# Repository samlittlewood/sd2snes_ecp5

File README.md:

Lattice ECP5 Transplant for SD2SNES
===================================

Based on https://github.com/mrehkopf/sd2snes

* Main changes are FPGA, RAM and power. The SNES interface and MCU are broadly the same as SD2SNES
* Prototype is populated with ECP5U-45F for easy development - 12F or 25F parts are available for same footprint. 
* MSU-1 DAC mods from https://github.com/DevLaTron/sd2snes
* USB-C (2.0) connector

Schematic: https://github.com/samlittlewood/sd2snes_ecp5/raw/main/RevB/sd2snes_ecp5.pdf

WARNING: This is still a prototype - it has managed to run games, but more than likely has some 'hilarious in hindsight' mistakes that have yet to be found.

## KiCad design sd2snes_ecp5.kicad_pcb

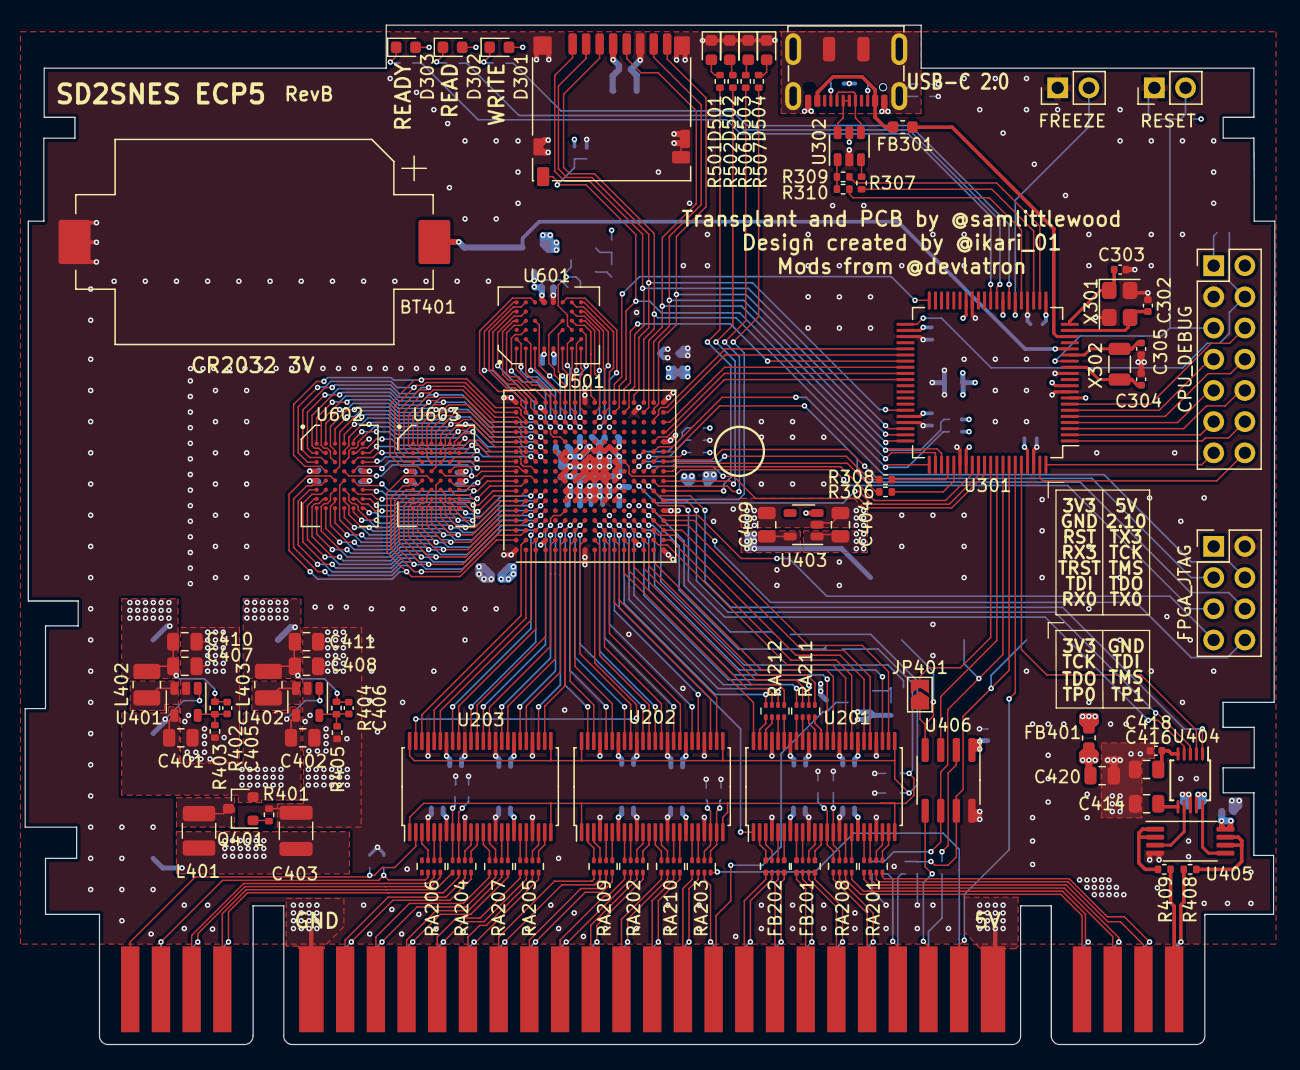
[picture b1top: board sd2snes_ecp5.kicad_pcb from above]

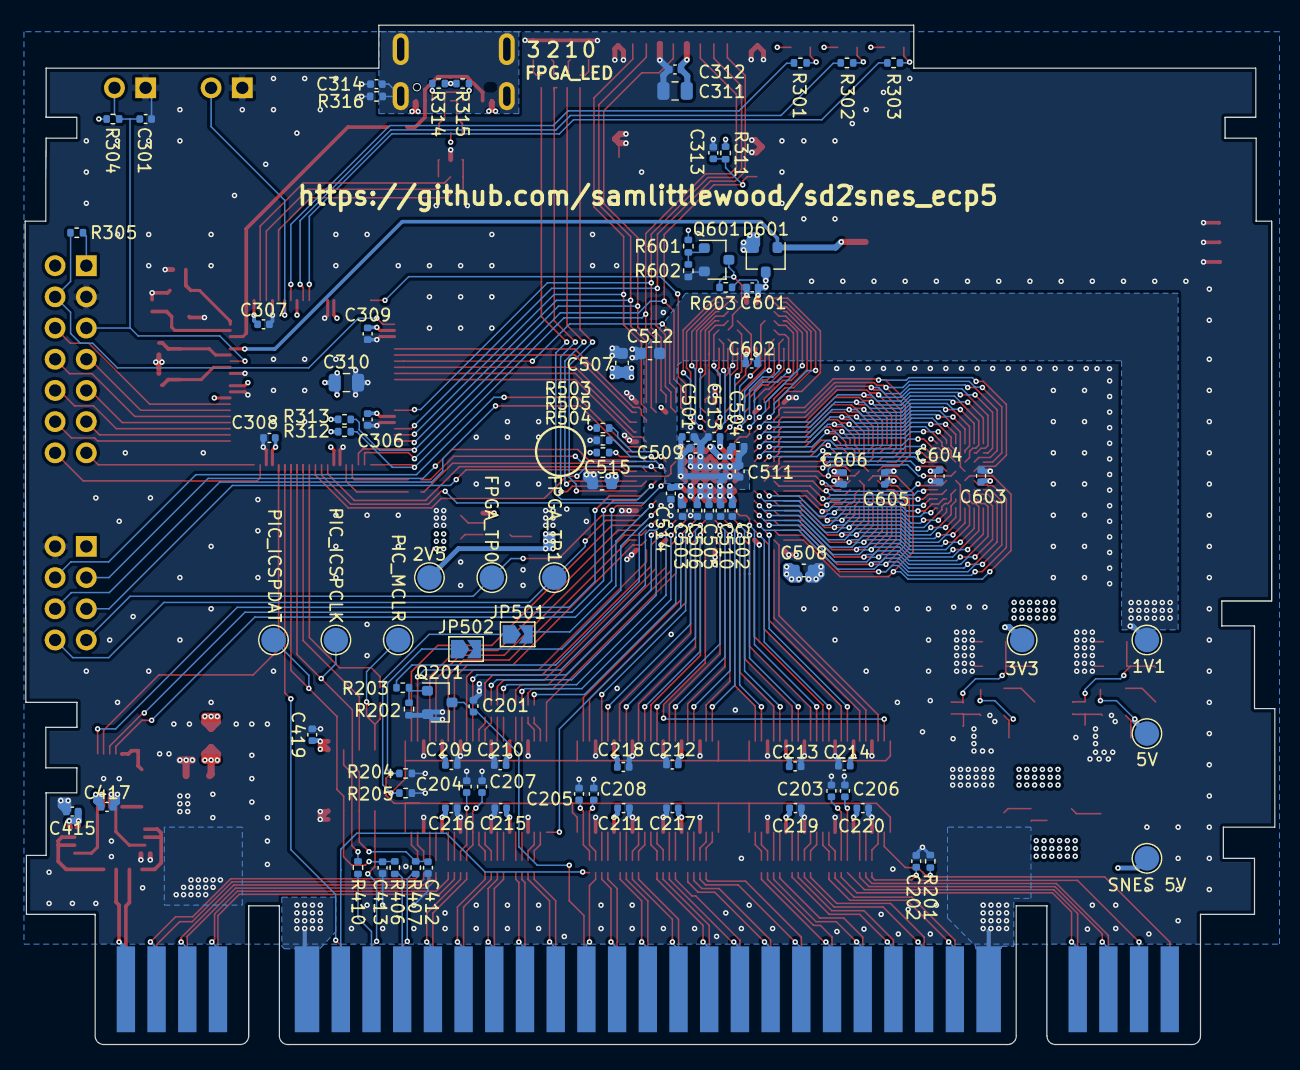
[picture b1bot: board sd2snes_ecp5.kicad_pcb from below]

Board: 4 copper layers, 101.8 x 83.0 mm, 184 parts (96 on the bottom side), 345 nets.

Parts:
BT401: Keystone 1060; BatteryHolder_Keystone_1060_1x2032
C201, C202, C203, C204, C205, C206, C207, C208, C304, C305: 10p; C_0402_1005Metric
C209, C210, C211, C212, C213, C214, C215, C216, C217, C218, C219, C220, C301, C306, C307, C308, C309, C312, C313, C314, C415, C417, C418, C419, C501, C502, C503, C504, C505, C506, C509, C510, C511, C513, C514, C601, C602, C603, C604, C605, C606: 100n; C_0402_1005Metric
C302, C303: 18p; C_0402_1005Metric
C310, C311, C414, C416: 10u; C_0805_2012Metric
C401, C402, C404: 4u7; C_0805_2012Metric
C403: 100u; C_1210_3225Metric
C405, C406: DNP; C_0402_1005Metric
C407, C408, C409, C410, C411: 22u; C_0805_2012Metric
C412, C413: 100p; C_0402_1005Metric
C420: 1u; C_0805_2012Metric
C507, C508, C512, C515: 2u2; C_0603_1608Metric
D301, D501: LED 2mA 1.7V, red; LED_0603_1608Metric
D302: LED 2mA 1.8V, yellow; LED_0603_1608Metric
D303, D502, D503, D504: LED 2mA 1.9V, green; LED_0603_1608Metric
D601: BAT54C; SOT-23
FB201, FB202: FB; R_Array_Convex_4x0402
FB301, FB401: FILTER; L_0603_1608Metric
J201: SNESCART_EXT
J301: USB-C; USB_C_Receptacle_JAE_DX07S016JA1
J302: MicroSD; microSD_HC_Hirose_DM3D-SF
J501: FPGA_JTAG; PinHeader_2x04_P2.54mm_Vertical
JP401: JUMPER; SolderJumper-2_P1.3mm_Open_TrianglePad1.0x1.5mm
JP501: TEST_OE; SolderJumper-2_P1.3mm_Open_TrianglePad1.0x1.5mm
JP502: TEST_DIR; SolderJumper-2_P1.3mm_Open_TrianglePad1.0x1.5mm
L401: 10u; L_1210_3225Metric
L402, L403: 2u2; L_1008_2520Metric
P301: RESET; PinHeader_1x02_P2.54mm_Vertical
P302: FREEZE; PinHeader_1x02_P2.54mm_Vertical
P303: CPU_DEBUG; PinHeader_2x07_P2.54mm_Vertical
Q201, Q601: MMBT2222A; SOT-23
Q401: IRLML6402PbF; SOT-23
R201: 270; R_0402_1005Metric
R202, R602: 100K; R_0402_1005Metric
R203, R204, R205, R312, R313, R601: 4K7; R_0402_1005Metric
R301, R302, R303, R406, R407, R410, R501, R502, R506, R507: 680; R_0402_1005Metric
R304, R305, R311, R316: 10K; R_0402_1005Metric
R306, R308, R503, R504, R505: 100; R_0402_1005Metric
R307, R309: 33; R_0402_1005Metric
R310: 1K5; R_0402_1005Metric
R314, R315: 5K1; R_0402_1005Metric
R401, R603: 20K; R_0402_1005Metric
R402, R404: 15K; R_0402_1005Metric
R403: 18K; R_0402_1005Metric
R405: 3K3; R_0402_1005Metric
R408, R409: 10; R_0402_1005Metric
RA201, RA202, RA203, RA204, RA205, RA206, RA207, RA208, RA209, RA210, RA211, RA212: 100; R_Array_Concave_4x0402
TP401: SNES 5V; TestPoint_Pad_D2.0mm
TP402: 5V; TestPoint_Pad_D2.0mm
TP403: 1V1; TestPoint_Pad_D2.0mm
TP404: 3V3; TestPoint_Pad_D2.0mm
TP405: 2V5; TestPoint_Pad_D2.0mm
TP406: PIC_ICSPDAT; TestPoint_Pad_D2.0mm
TP407: PIC_ICSPCLK; TestPoint_Pad_D2.0mm
TP408: PIC_MCLR; TestPoint_Pad_D2.0mm
TP501: FPGA_TP0; TestPoint_Pad_D2.0mm
TP502: FPGA_TP1; TestPoint_Pad_D2.0mm
U201, U202, U203: 74ALVC164245DGG; TSSOP-48_6.1x12.5mm_P0.5mm
U301: LPC1756; LQFP-80_12x12mm_P0.5mm
U302: USBLC6-2SC6; SOT-23-6
U401, U402: TLV62568DBV; SOT-23-5
U403: TLV73325PDBV; SOT-23-5
U404: CS4344; TSSOP-10_3x3mm_P0.5mm
U405: TS9222; TSSOP-8_4.4x3mm_P0.65mm
U406: PIC12F629-ISN; SOIC-8_3.9x4.9mm_P1.27mm
U501: ECP5U_45_CABGA256; Lattice_caBGA-256_14.0x14.0mm_Layout16x`6_P0.8mm_Ball0.4mm_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
U601: IS62WV5128EBLL-45BLI; TFBGA-36_6x8_6.0x8.0mm
U602, U603: IS66WVE4M16EBLL-70BLI; TFBGA-48_6x8_6.0x8.0mm
X301: 8MHz; Crystal_SMD_3225-4Pin_3.2x2.5mm
X302: 32.768kHz; Crystal_SMD_3215-2Pin_3.2x1.5mm

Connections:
+1V1: C405.1, C407.1, C410.1, C509.1, C510.1, C511.1, C512.1, L402.2, R402.1, TP403.1, U501.G6, U501.G7, U501.G9, U501.L8, U501.L9, U501.L10
+2V5: C409.1, C513.1, C514.1, C515.1, TP405.1, U403.5, U501.G11, U501.L7
+3.3VDAC: C415.1, C417.1, C420.1, FB401.1, U404.9, U405.8
+3V3: C209.1, C210.1, C211.1, C212.1, C213.1, C214.1, C306.1, C307.1, C308.1, C309.1, C310.1, C311.1, C312.1, C404.1, C406.1, C408.1, C411.1, C501.1, C502.1, C503.1, C504.1, C505.1, C506.1, C507.1, C508.1, C603.1, C604.1, C605.1, C606.1, D301.2, D302.2, D303.2, D601.2, FB401.2, J302.4, J501.1, L403.2, P303.1, R304.2, R305.2, R311.2, R312.1, R313.1, R404.1, R503.2, R504.2, R601.2, TP404.1, U201.31, U201.42, U202.31, U202.42, U203.31, U203.42, U301.8, U301.10, U301.21, U301.34, U301.42, U301.56, U301.67, U301.77, U302.5, U403.1, U403.3, U501.F6, U501.F7, U501.F10, U501.F11, U501.H6, U501.H7, U501.H11, U501.J6, U501.J7, U501.J11, U501.K11, U501.L6, U501.L11, U602.A6, U602.D6, U602.E1, U603.A6, U603.D6, U603.E1
+5V: C215.1, C216.1, C217.1, C218.1, C219.1, C220.1, C401.1, C402.1, C419.1, P303.2, Q401.2, TP402.1, U201.7, U201.18, U202.7, U202.18, U203.7, U203.18, U401.1, U401.4, U402.1, U402.4, U406.1
+5VL: C403.1, J201.27, J201.58, L401.2, TP401.1
+BATT: BT401.1, D601.1, U301.16
/FPGA/CFG_0: R503.1, U501.N10
/FPGA/CFG_1: R505.1, U501.P10
/FPGA/CFG_2: R504.1, U501.R10
/FPGA/FPGA_LED0: R501.1, U501.T7
/FPGA/FPGA_LED1: R502.1, U501.T8
/FPGA/FPGA_LED2: R506.1, U501.R8
/FPGA/FPGA_LED3: R507.1, U501.P8
/FPGA/FPGA_TCK: J501.3, U501.T10
/FPGA/FPGA_TDI: J501.4, U501.R11
/FPGA/FPGA_TDO: J501.5, U501.M10
/FPGA/FPGA_TMS: J501.6, U501.T11
/FPGA/FPGA_TP0: J501.7, TP501.1, U501.R5
/FPGA/FPGA_TP1: J501.8, TP502.1, U501.T4
/MCU/CC1: J301.A5, R314.1
/MCU/CC2: J301.B5, R315.1
/MCU/D+: J301.A6, J301.B6, U302.6
/MCU/D-: J301.A7, J301.B7, U302.4
/MCU/SHIELD: C314.1, J301.S1, R316.2
/Memory/SRAM_VDD: C601.1, C602.1, D601.3, R603.1, U601.D6, U601.E1
/Memory/~SDRAM_CS: Q601.3, R603.2, U601.G3
/Power Supply / Misc./AOUTL: U404.7, U405.3
/Power Supply / Misc./AOUTR: U404.10, U405.5
/Power Supply / Misc./CIC_CLK: R410.1, U406.2
/Power Supply / Misc./FILT: C414.1, U404.6
/Power Supply / Misc./VQ: C416.1, C418.1, U404.5
/SNES Slot/SNES_EXT_A0: J201.17, RA203.1
/SNES Slot/SNES_EXT_A1: J201.16, RA210.3
/SNES Slot/SNES_EXT_A2: J201.15, RA210.1
/SNES Slot/SNES_EXT_A3: J201.14, RA202.3
/SNES Slot/SNES_EXT_A4: J201.13, RA202.1
/SNES Slot/SNES_EXT_A5: J201.12, RA209.3
/SNES Slot/SNES_EXT_A6: J201.11, RA209.1
/SNES Slot/SNES_EXT_A7: J201.10, RA205.3
/SNES Slot/SNES_EXT_A8: J201.9, RA205.1
/SNES Slot/SNES_EXT_A9: J201.8, RA207.3
/SNES Slot/SNES_EXT_A10: J201.7, RA207.1
/SNES Slot/SNES_EXT_A11: J201.6, RA204.3
/SNES Slot/SNES_EXT_A12: J201.37, RA204.4
/SNES Slot/SNES_EXT_A13: J201.38, RA207.2
/SNES Slot/SNES_EXT_A14: J201.39, RA207.4
/SNES Slot/SNES_EXT_A15: J201.40, RA205.2
/SNES Slot/SNES_EXT_A16: J201.41, RA205.4
/SNES Slot/SNES_EXT_A17: J201.42, RA209.2
/SNES Slot/SNES_EXT_A18: J201.43, RA209.4
/SNES Slot/SNES_EXT_A19: J201.44, RA202.2
/SNES Slot/SNES_EXT_A20: J201.45, RA202.4
/SNES Slot/SNES_EXT_A21: J201.46, RA210.2
/SNES Slot/SNES_EXT_A22: J201.47, RA210.4
/SNES Slot/SNES_EXT_A23: J201.48, RA203.2
/SNES Slot/SNES_EXT_CPU_CLK: J201.57, RA203.4
/SNES Slot/SNES_EXT_D0: FB202.1, J201.19
/SNES Slot/SNES_EXT_D1: FB202.3, J201.20
/SNES Slot/SNES_EXT_D2: FB201.1, J201.21
/SNES Slot/SNES_EXT_D3: FB201.3, J201.22
/SNES Slot/SNES_EXT_D4: FB202.2, J201.50
/SNES Slot/SNES_EXT_D5: FB202.4, J201.51
/SNES Slot/SNES_EXT_D6: FB201.2, J201.52
/SNES Slot/SNES_EXT_D7: FB201.4, J201.53
/SNES Slot/SNES_EXT_PA0: J201.28, RA208.3
/SNES Slot/SNES_EXT_PA1: J201.59, RA208.4
/SNES Slot/SNES_EXT_PA2: J201.29, RA201.1
/SNES Slot/SNES_EXT_PA3: J201.60, RA201.2
/SNES Slot/SNES_EXT_PA4: J201.30, RA201.3
/SNES Slot/SNES_EXT_PA5: J201.61, RA201.4
/SNES Slot/SNES_EXT_PA6: J201.3, RA206.3
/SNES Slot/SNES_EXT_PA7: J201.34, RA206.4
/SNES Slot/SNES_EXT_REFRESH: C202.1, J201.33, RA206.2
/SNES Slot/SNES_EXT_SYS_CLK: J201.1, R201.2, U203.2
/SNES Slot/~SNES_EXT_IRQ: C201.1, J201.18, Q201.3
/SNES Slot/~SNES_EXT_PARD: J201.4, RA204.1
/SNES Slot/~SNES_EXT_PAWR: J201.35, RA204.2
/SNES Slot/~SNES_EXT_RD: J201.23, RA208.1
/SNES Slot/~SNES_EXT_ROMSEL: J201.49, RA203.3
/SNES Slot/~SNES_EXT_WR: J201.54, RA208.2
AUDIO_L: J201.31, R409.2
AUDIO_R: J201.62, R408.2
CIC_DATA0: C413.1, R406.1, TP406.1, U301.74, U406.7
CIC_DATA1: C412.1, R407.2, TP407.1, U301.73, U406.6
CIC_MCLR: JP401.2, U301.71
CIC_RESET: J201.25, U406.5
CIC_STATUS: U301.72, U406.3
DAC_LRCK: U404.3, U501.T6
DAC_MCLK: U404.4, U501.R6
DAC_SDOUT: U404.1, U501.R7
EXT_CIC_CLK: J201.56, R410.2
EXT_CIC_DATA0: J201.55, R406.2
EXT_CIC_DATA1: J201.24, R407.1
EXT_TDI: P303.11, U301.2
EXT_TDO: P303.12, U301.1
FPGA_CCLK: R308.2, U501.N9
FPGA_CLKIN: U301.40, U501.L16
FPGA_DI: U301.69, U501.N8
FPGA_DONE: U301.70, U501.P9
GND: BT401.2, C201.2, C202.2, C203.2, C204.2, C205.2, C206.2, C207.2, C208.2, C209.2, C210.2, C211.2, C212.2, C213.2, C214.2, C215.2, C216.2, C217.2, C218.2, C219.2, C220.2, C301.2, C302.2, C303.2, C304.2, C305.2, C306.2, C307.2, C308.2, C309.2, C310.2, C311.2, C312.2, C313.2, C314.2, C401.2, C402.2, C403.2, C404.2, C407.2, C408.2, C409.2, C410.2, C411.2, C412.2, C413.2, C414.2, C415.2, C416.2, C417.2, C418.2, C419.2, C420.2, C501.2, C502.2, C503.2, C504.2, C505.2, C506.2, C507.2, C508.2, C509.2, C510.2, C511.2, C512.2, C513.2, C514.2, C515.2, C601.2, C602.2, C603.2, C604.2, C605.2, C606.2, D501.1, D502.1, D503.1, D504.1, J201.5, J201.36, J301.A1, J301.A12, J301.B1, J301.B12, J302.6, J302.9, J302.11, J501.2, P301.1, P302.1, P303.3, Q201.2, Q601.2, R201.1, R202.2, R204.1, R205.1, R314.2, R315.2, R316.1, R401.1, R403.2, R405.2, R505.2, R602.2, U201.4, U201.10, U201.15, U201.21, U201.28, U201.34, U201.39, U201.45, U202.4, U202.10, U202.15, U202.21, U202.28, U202.34, U202.39, U202.45, U203.4, U203.10, U203.15, U203.21, U203.28, U203.34, U203.39, U203.45, U301.9, U301.12, U301.24, U301.33, U301.43, U301.57, U301.66, U301.78, U302.2, U401.2, U402.2, U403.2, U404.8, U405.4, U406.8, U501.A1, U501.A16, U501.D2, U501.D15, U501.F8, U501.F9, U501.G8, U501.G10, U501.H1, U501.H8, U501.H9, U501.H10, U501.H16, U501.J8, U501.J9, U501.J10, U501.K6, U501.K7, U501.K8, U501.K9, U501.K10, U501.N2, U501.N15, U501.T1, U501.T5, U501.T12, U501.T16, U601.D1, U601.E6, U602.D1, U602.E6, U603.D1, U603.E6, X301.2, X301.4
unnamed: C203.1, RA204.7, U203.9
unnamed: C204.1, RA208.7, U201.14
unnamed: C205.1, RA203.5, U202.23
unnamed: C206.1, RA204.8, U203.8
unnamed: C207.1, RA208.8, U201.13
unnamed: C208.1, RA203.6, U202.22
unnamed: C302.1, U301.19, X301.3
unnamed: C303.1, U301.20, X301.1
unnamed: C304.1, U301.13, X302.1
unnamed: C305.1, U301.15, X302.2
unnamed: C405.2, R402.2, R403.1, U401.5
unnamed: C406.2, R404.2, R405.1, U402.5
unnamed: D301.1, R301.1
unnamed: D302.1, R302.2
unnamed: D303.1, R303.2
unnamed: D501.2, R501.2
unnamed: D502.2, R502.2
unnamed: D503.2, R506.2
unnamed: D504.2, R507.2
unnamed: FB201.5, U201.12
unnamed: FB201.6, U201.11
unnamed: FB201.7, U201.9
unnamed: FB201.8, U201.8
unnamed: FB202.5, U201.6
unnamed: FB202.6, U201.5
unnamed: FB202.7, U201.3
unnamed: FB202.8, U201.2
unnamed: FB301.1, J301.A4, J301.A9, J301.B4, J301.B9
unnamed: JP401.1, TP408.1, U406.4
unnamed: JP501.2, U501.P6
unnamed: JP502.2, U501.P5
unnamed: L401.1, Q401.3
unnamed: L402.1, U401.3
unnamed: L403.1, U402.3
unnamed: P302.2, U301.26
unnamed: Q201.1, R202.1, R203.2
unnamed: Q401.1, R401.2
unnamed: Q601.1, R601.1, R602.1
unnamed: R306.2, U301.65
unnamed: R307.1, U302.3
unnamed: R307.2, U301.23
unnamed: R308.1, U301.64
unnamed: R309.1, R310.1, U302.1
unnamed: R309.2, U301.22
unnamed: R310.2, U301.25
unnamed: R408.1, U405.6, U405.7
unnamed: R409.1, U405.1, U405.2
unnamed: RA201.5, U201.23
unnamed: RA201.6, U201.22
unnamed: RA201.7, U201.20
unnamed: RA201.8, U201.19
unnamed: RA202.5, U202.12
unnamed: RA202.6, U202.11
unnamed: RA202.7, U202.9
unnamed: RA202.8, U202.8
unnamed: RA203.7, U202.20
unnamed: RA203.8, U202.19
unnamed: RA204.5, U203.12
unnamed: RA204.6, U203.11
unnamed: RA205.5, U203.23
unnamed: RA205.6, U203.22
unnamed: RA205.7, U203.20
unnamed: RA205.8, U203.19
unnamed: RA206.5, U203.6
unnamed: RA206.6, U203.5
unnamed: RA206.7, U203.3
unnamed: RA207.5, U203.17
unnamed: RA207.6, U203.16
unnamed: RA207.7, U203.14
unnamed: RA207.8, U203.13
unnamed: RA208.5, U201.17
unnamed: RA208.6, U201.16
unnamed: RA209.5, U202.6
unnamed: RA209.6, U202.5
unnamed: RA209.7, U202.3
unnamed: RA209.8, U202.2
unnamed: RA210.5, U202.17
unnamed: RA210.6, U202.16
unnamed: RA210.7, U202.14
unnamed: RA210.8, U202.13
unnamed: RA211.1, U201.41
unnamed: RA211.2, U201.40
unnamed: RA211.3, U201.38
unnamed: RA211.4, U201.37
unnamed: RA212.1, U201.47
unnamed: RA212.2, U201.46
unnamed: RA212.3, U201.44
unnamed: RA212.4, U201.43
P2.10: P303.4, R305.1, U301.41
RAM_ADDR[0]: U501.E15, U601.A1
RAM_ADDR[1]: U501.E14, U601.A2
RAM_ADDR[2]: U501.F13, U601.B2
RAM_ADDR[3]: U501.C16, U601.A4
RAM_ADDR[4]: U501.D16, U601.B4
RAM_ADDR[5]: U501.F14, U601.C4
RAM_ADDR[6]: U501.C15, U601.A5
RAM_ADDR[7]: U501.D14, U601.B5
RAM_ADDR[8]: U501.C14, U601.A6
RAM_ADDR[9]: U501.H15, U601.H1
RAM_ADDR[10]: U501.H13, U601.H2
RAM_ADDR[11]: U501.H14, U601.H3
RAM_ADDR[12]: U501.J15, U601.H4
RAM_ADDR[13]: U501.K16, U601.H5
RAM_ADDR[14]: U501.K15, U601.H6
RAM_ADDR[15]: U501.J14, U601.G5
RAM_ADDR[16]: U501.J16, U601.G4
RAM_ADDR[17]: U501.F16, U601.F4
RAM_ADDR[18]: U501.G13, U601.F3
RAM_DATA[0]: U501.B16, U601.B6
RAM_DATA[1]: U501.B15, U601.C6
RAM_DATA[2]: U501.K14, U601.F6
RAM_DATA[3]: U501.J13, U601.G6
RAM_DATA[4]: U501.E16, U601.B1
RAM_DATA[5]: U501.F15, U601.C1
RAM_DATA[6]: U501.G15, U601.F1
RAM_DATA[7]: U501.G16, U601.G1
ROM_ADDR[0]: U501.B11, U602.A3, U603.A3
ROM_ADDR[1]: U501.A12, U602.A4, U603.A4
ROM_ADDR[2]: U501.B10, U602.A5, U603.A5
ROM_ADDR[3]: U501.D12, U602.B3, U603.B3
ROM_ADDR[4]: U501.D11, U602.B4, U603.B4
ROM_ADDR[5]: U501.C13, U602.C3, U603.C3
ROM_ADDR[6]: U501.C11, U602.C4, U603.C4
ROM_ADDR[7]: U501.A9, U602.D4, U603.D4
ROM_ADDR[8]: U501.C5, U602.H2, U603.H2
ROM_ADDR[9]: U501.D6, U602.H3, U603.H3
ROM_ADDR[10]: U501.C6, U602.H4, U603.H4
ROM_ADDR[11]: U501.D7, U602.H5, U603.H5
ROM_ADDR[12]: U501.B5, U602.G3, U603.G3
ROM_ADDR[13]: U501.B6, U602.G4, U603.G4
ROM_ADDR[14]: U501.A4, U602.F3, U603.F3
ROM_ADDR[15]: U501.A6, U602.F4, U603.F4
ROM_ADDR[16]: U501.A5, U602.E4, U603.E4
ROM_ADDR[17]: U501.C12, U602.D3, U603.D3
ROM_ADDR[18]: U501.D5, U602.H1, U603.H1
ROM_ADDR[19]: U501.B4, U602.G2, U603.G2
ROM_ADDR[20]: U501.C7, U602.H6, U603.H6
ROM_ADDR[21]: U501.A2, U602.E3, U603.E3
ROM_DATA[0]: U501.C9, U602.B6, U603.B6
ROM_DATA[1]: U501.C10, U602.C5, U603.C5
ROM_DATA[2]: U501.A10, U602.C6, U603.C6
ROM_DATA[3]: U501.B9, U602.D5, U603.D5
ROM_DATA[4]: U501.C8, U602.E5, U603.E5
ROM_DATA[5]: U501.B8, U602.F5, U603.F5
ROM_DATA[6]: U501.A8, U602.F6, U603.F6
ROM_DATA[7]: U501.A7, U602.G6, U603.G6
ROM_DATA[8]: U501.A14, U602.B1, U603.B1
ROM_DATA[9]: U501.A15, U602.C1, U603.C1
ROM_DATA[10]: U501.B13, U602.C2, U603.C2
ROM_DATA[11]: U501.B14, U602.D2, U603.D2
ROM_DATA[12]: U501.B3, U602.E2, U603.E2
ROM_DATA[13]: U501.A3, U602.F2, U603.F2
ROM_DATA[14]: U501.D4, U602.F1, U603.F1
ROM_DATA[15]: U501.C4, U602.G1, U603.G1
RX0: P303.13, U301.80
RX3: P303.7, U301.6
SD_CLK: J302.5, R313.2, U301.63, U501.P15
SD_CMD: J302.3, R312.2, U301.61, U501.P16
SD_DAT[0]: J302.7, U301.60, U501.R16
SD_DAT[1]: J302.8, U301.59, U501.R15
SD_DAT[2]: J302.1, U301.58, U501.M15
SD_DAT[3]: J302.2, U301.55, U501.N16
SD_DET: C313.1, J302.10, R311.1, U301.62, U501.L15
SNES_ADDR_IN[0]: U202.30, U501.K3
SNES_ADDR_IN[1]: U202.33, U501.J4
SNES_ADDR_IN[2]: U202.36, U501.J3
SNES_ADDR_IN[3]: U202.38, U501.H3
SNES_ADDR_IN[4]: U202.41, U501.H4
SNES_ADDR_IN[5]: U202.44, U501.G3
SNES_ADDR_IN[6]: U202.47, U501.G4
SNES_ADDR_IN[7]: U203.27, U501.F3
SNES_ADDR_IN[8]: U203.30, U501.F4
SNES_ADDR_IN[9]: U203.33, U501.E3
SNES_ADDR_IN[10]: U203.36, U501.F5
SNES_ADDR_IN[11]: U203.38, U501.D3
SNES_ADDR_IN[12]: U203.37, U501.D1
SNES_ADDR_IN[13]: U203.35, U501.E2
SNES_ADDR_IN[14]: U203.32, U501.E1
SNES_ADDR_IN[15]: U203.29, U501.F2
SNES_ADDR_IN[16]: U203.26, U501.F1
SNES_ADDR_IN[17]: U202.46, U501.G2
SNES_ADDR_IN[18]: U202.43, U501.G1
SNES_ADDR_IN[19]: U202.40, U501.H2
SNES_ADDR_IN[20]: U202.37, U501.J2
SNES_ADDR_IN[21]: U202.35, U501.K1
SNES_ADDR_IN[22]: U202.32, U501.K2
SNES_ADDR_IN[23]: U202.29, U501.K4
SNES_CPU_CLK_IN: U202.26, U501.L2
SNES_DATABUS_DIR: U201.1, U501.L3
SNES_DATA[0]: RA212.8, U501.L4
SNES_DATA[1]: RA212.6, U501.M3
SNES_DATA[2]: RA211.8, U501.M4
SNES_DATA[3]: RA211.6, U501.N3
SNES_DATA[4]: RA212.7, U501.M2
SNES_DATA[5]: RA212.5, U501.N1
SNES_DATA[6]: RA211.7, U501.P1
SNES_DATA[7]: RA211.5, U501.P2
SNES_IRQ: R203.1, U501.P4
SNES_PA_IN[0]: U201.33, U501.R2
SNES_PA_IN[1]: U201.32, U501.T2
SNES_PA_IN[2]: U201.30, U501.R3
SNES_PA_IN[3]: U201.29, U501.T3
SNES_PA_IN[4]: U201.27, U501.N4
SNES_PA_IN[5]: U201.26, U501.R4
SNES_PA_IN[6]: U203.44, U501.B1
SNES_PA_IN[7]: U203.43, U501.C2
SNES_REFRESH: U203.46, U501.B2
SNES_SYSCLK: U203.47, U501.J1
SNES_TEST_DIR: JP502.1, R204.2, U201.24, U202.1, U202.24, U203.1, U203.24
SPI_MISO: U301.46, U501.T15
SPI_MOSI: U301.45, U501.R14
SPI_SCK: U301.47, U501.M16
SPI_SS: U301.48, U501.T14
TCK: P303.8, U301.5
TMS: P303.10, U301.3
TX0: P303.14, U301.79
TX3: P303.6, U301.7
USB_VBUS: FB301.2, U301.18
~DAC_DEM: U301.76, U404.2
~FPGA_INIT: U301.68, U501.T9
~FPGA_PROGRAM: R306.1, U501.R9
~LED_READ: R302.1, U301.29
~LED_READY: R303.1, U301.30
~LED_WRITE: R301.2, U301.27
~MCU_IRQ: U301.50, U501.R12
~MCU_RDY: U301.49, U501.T13
~RAM_OE: U501.G14, U601.G2
~RAM_WE: U501.F12, U601.B3
~RESET: C301.1, P301.2, P303.5, R304.1, U301.14
~ROM0_CE: U501.D10, U602.B5
~ROM1_CE: U501.A11, U603.B5
~ROM_BHE: U501.D13, U602.B2, U603.B2
~ROM_BLE: U501.B12, U602.A1, U603.A1
~ROM_OE: U501.A13, U602.A2, U603.A2
~ROM_WE: U501.B7, U602.G5, U603.G5
~SNES_DATABUS_OE: U201.48, U501.M1
~SNES_PARD_IN: U203.41, U501.C3
~SNES_PAWR_IN: U203.40, U501.C1
~SNES_READ_IN: U201.36, U501.P3
~SNES_RESET: J201.26, U301.75
~SNES_ROMSEL_IN: U202.27, U501.L1
~SNES_TEST_OE: JP501.1, R205.2, U201.25, U202.25, U202.48, U203.25, U203.48
~SNES_WRITE_IN: U201.35, U501.R1
~TRST: P303.9, U301.4

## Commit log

2021-02-17 First commit - moving PCB into seperate repo. for the momwnt.
2021-02-17 RevB Gerbers and PDF.
2021-02-17 Add README.
2021-02-17 Tidy up README.
2021-02-17 Updated README.
2021-02-18 Fix labels on snes slot lines.
